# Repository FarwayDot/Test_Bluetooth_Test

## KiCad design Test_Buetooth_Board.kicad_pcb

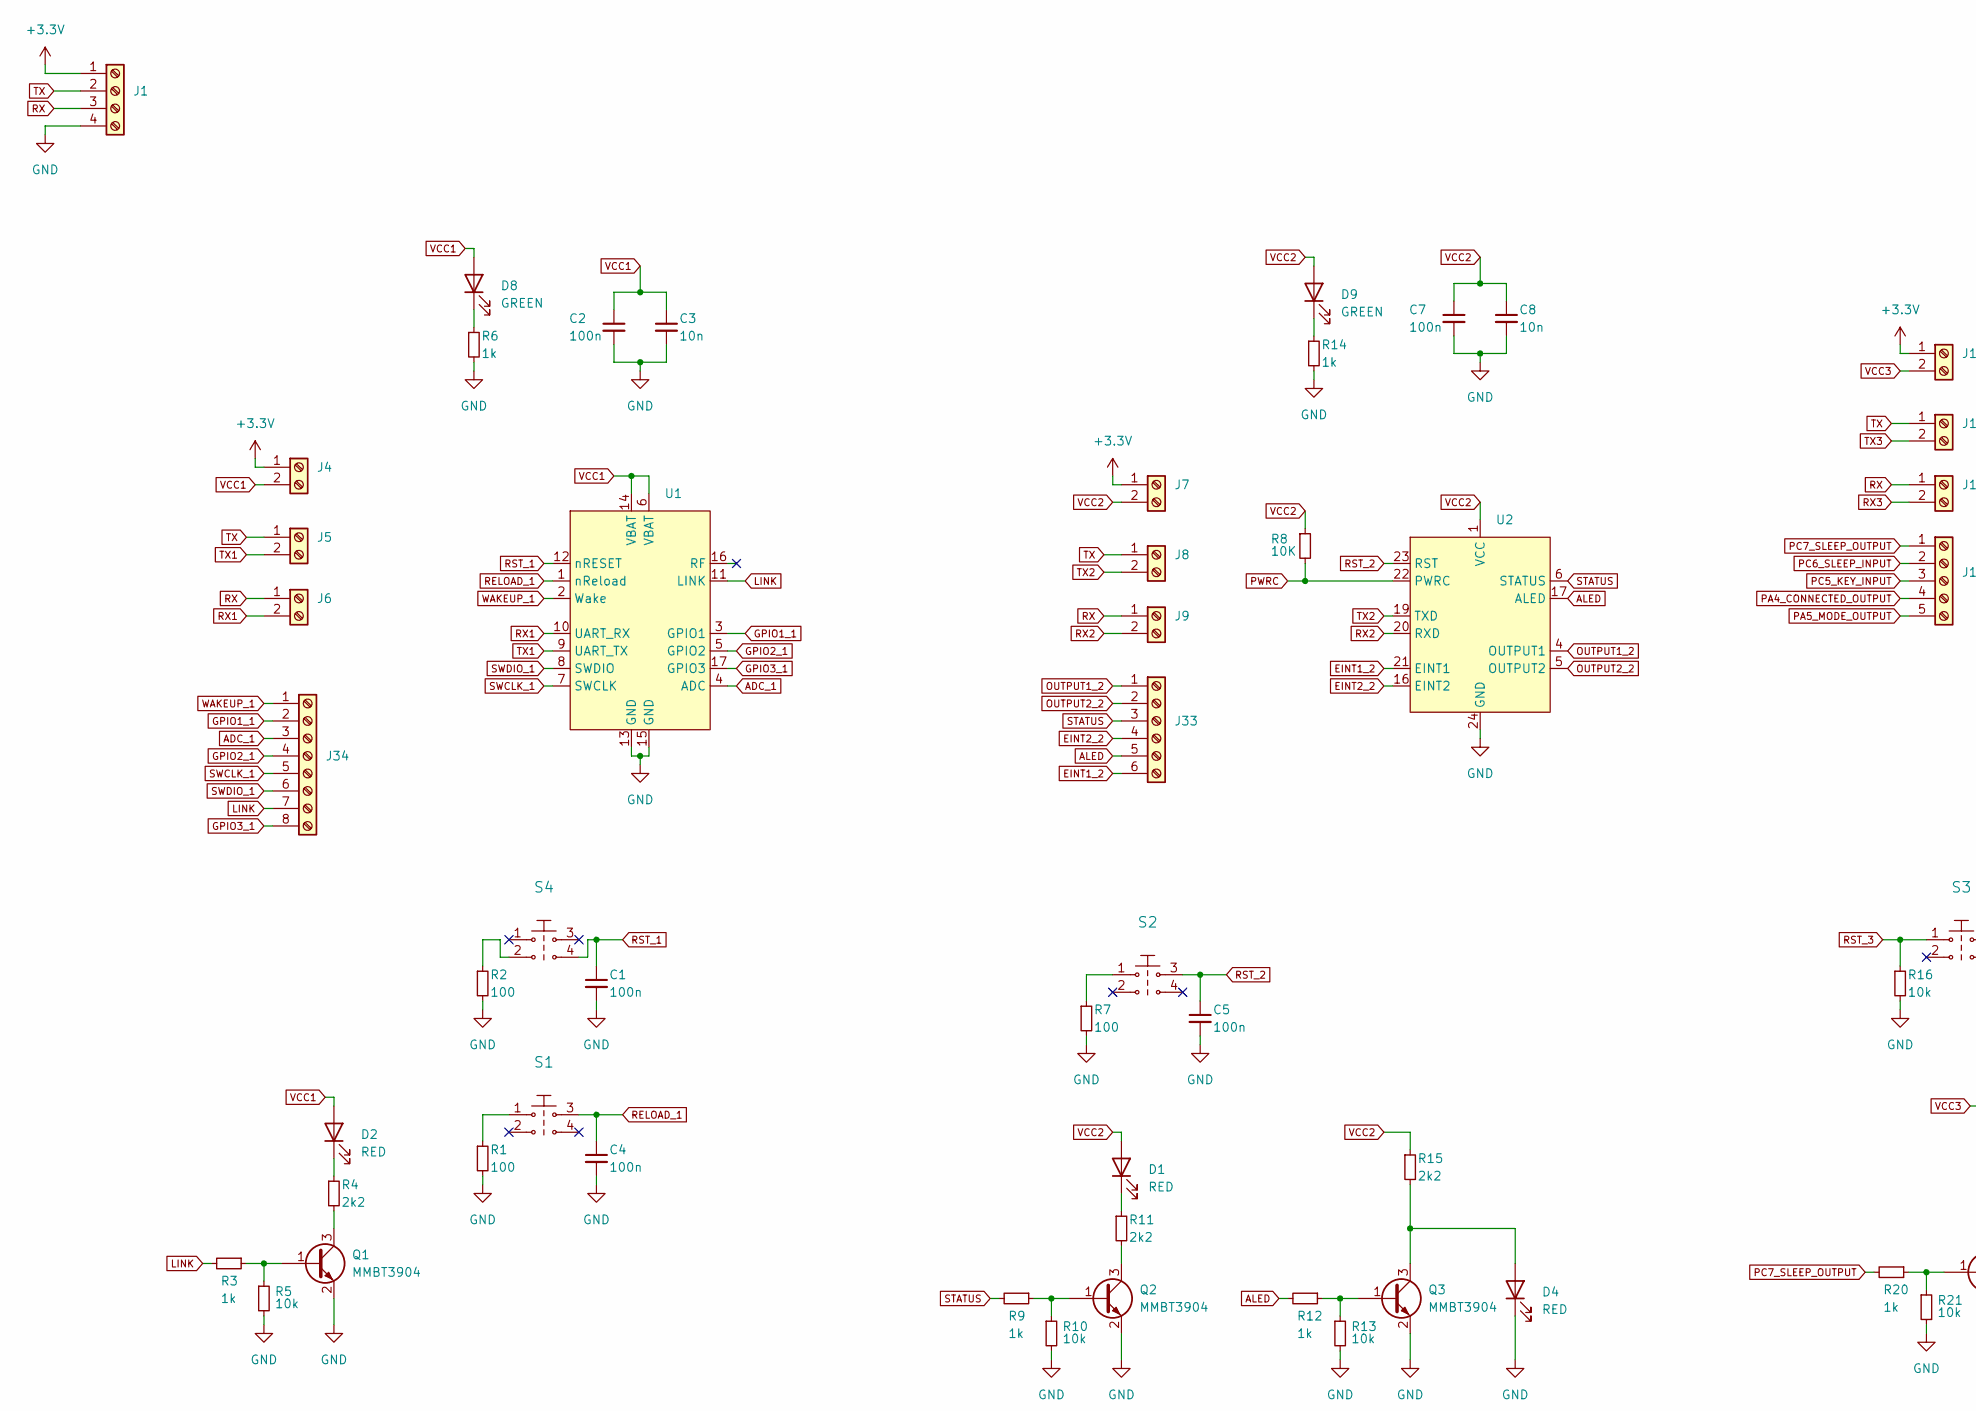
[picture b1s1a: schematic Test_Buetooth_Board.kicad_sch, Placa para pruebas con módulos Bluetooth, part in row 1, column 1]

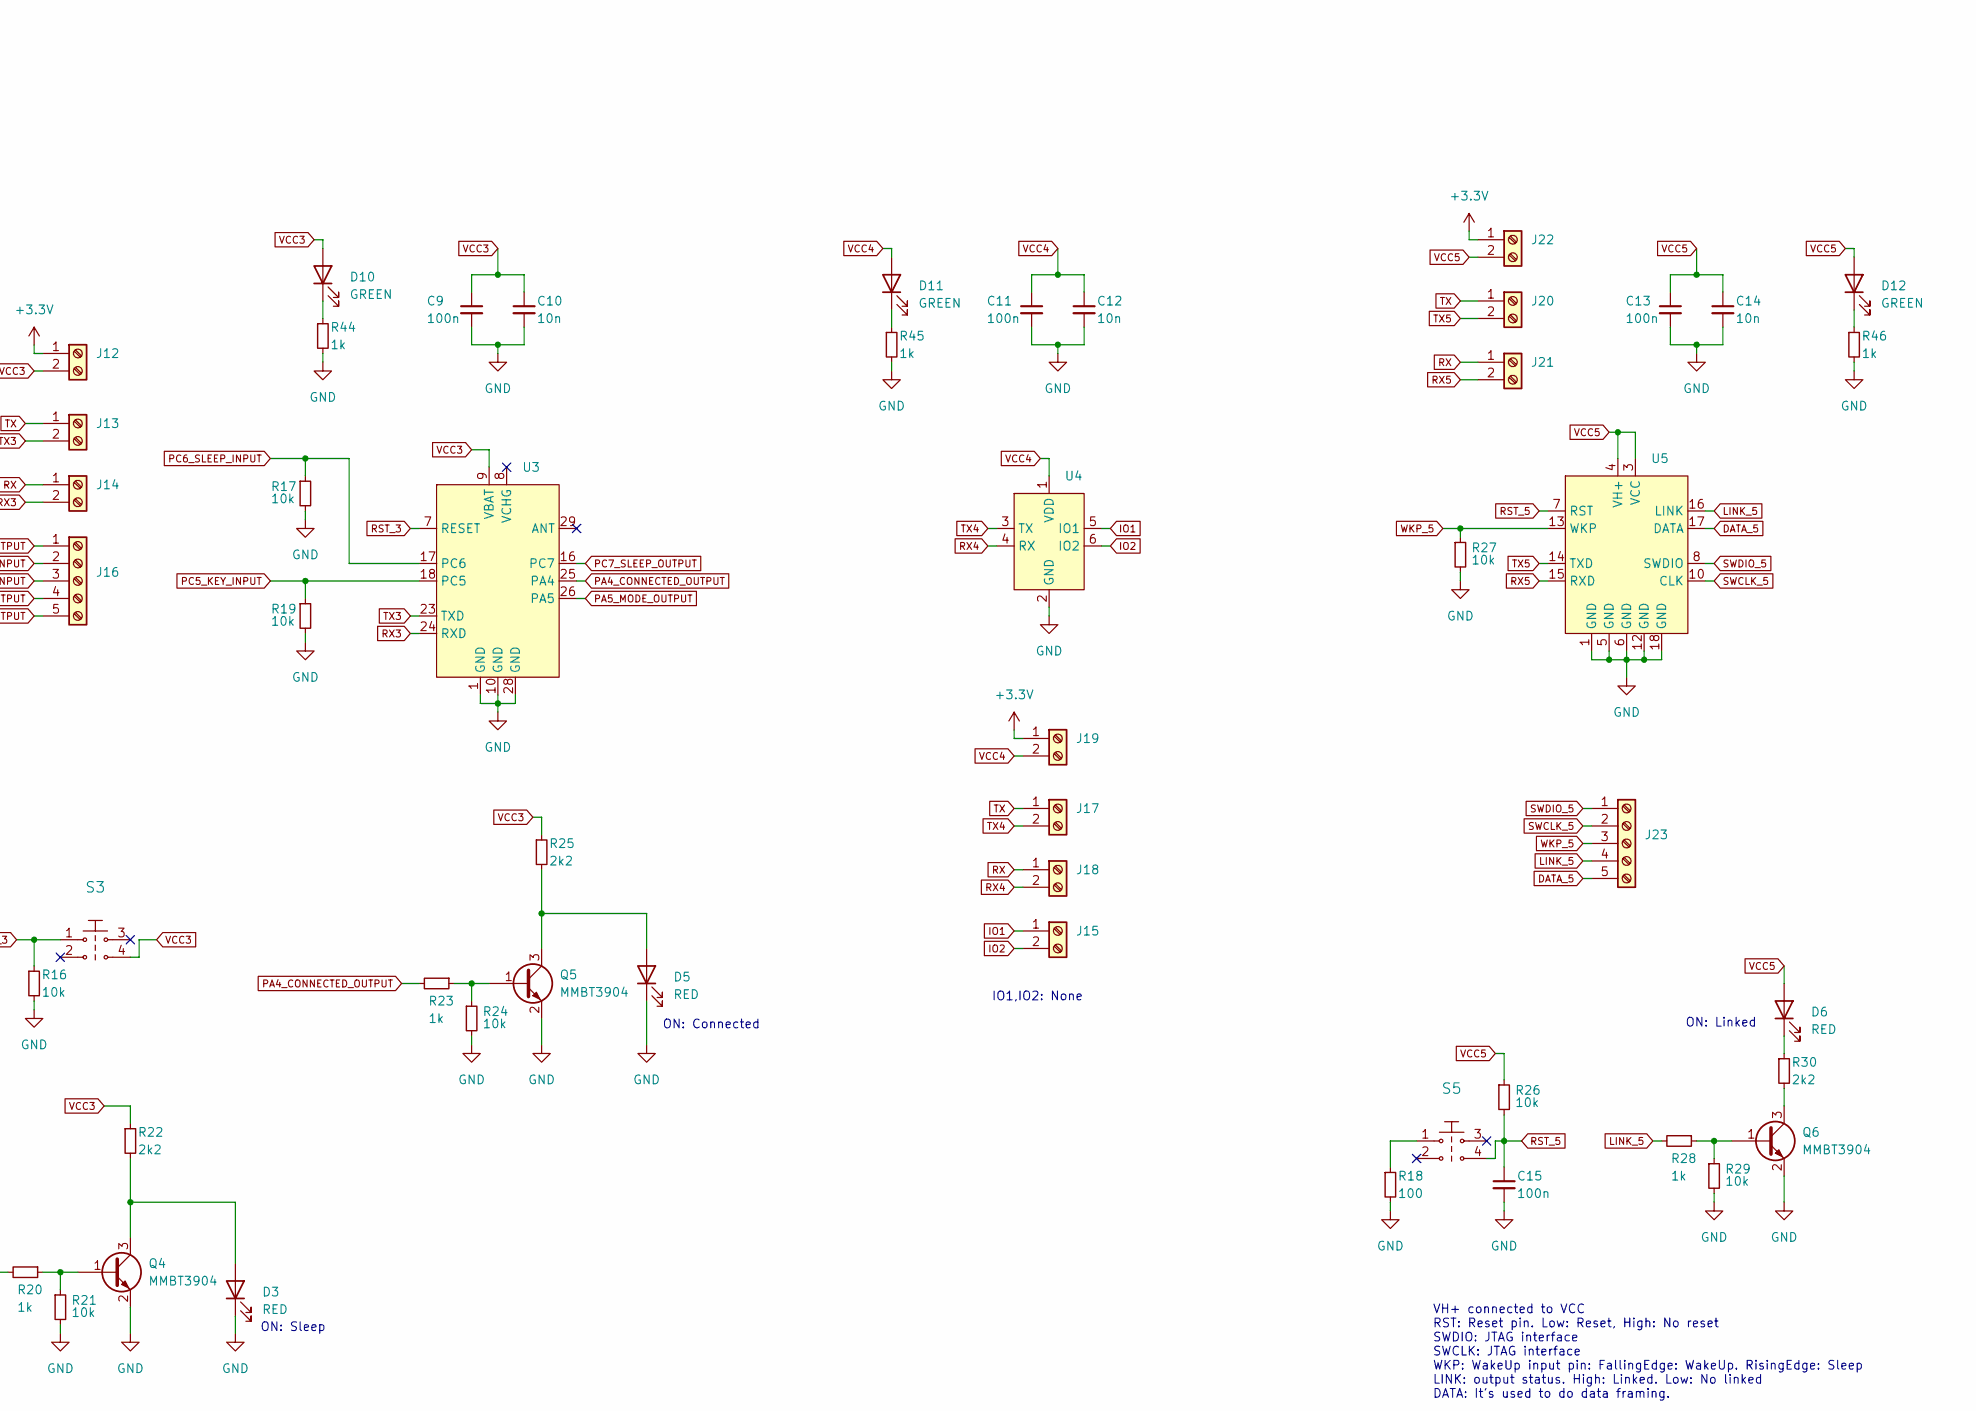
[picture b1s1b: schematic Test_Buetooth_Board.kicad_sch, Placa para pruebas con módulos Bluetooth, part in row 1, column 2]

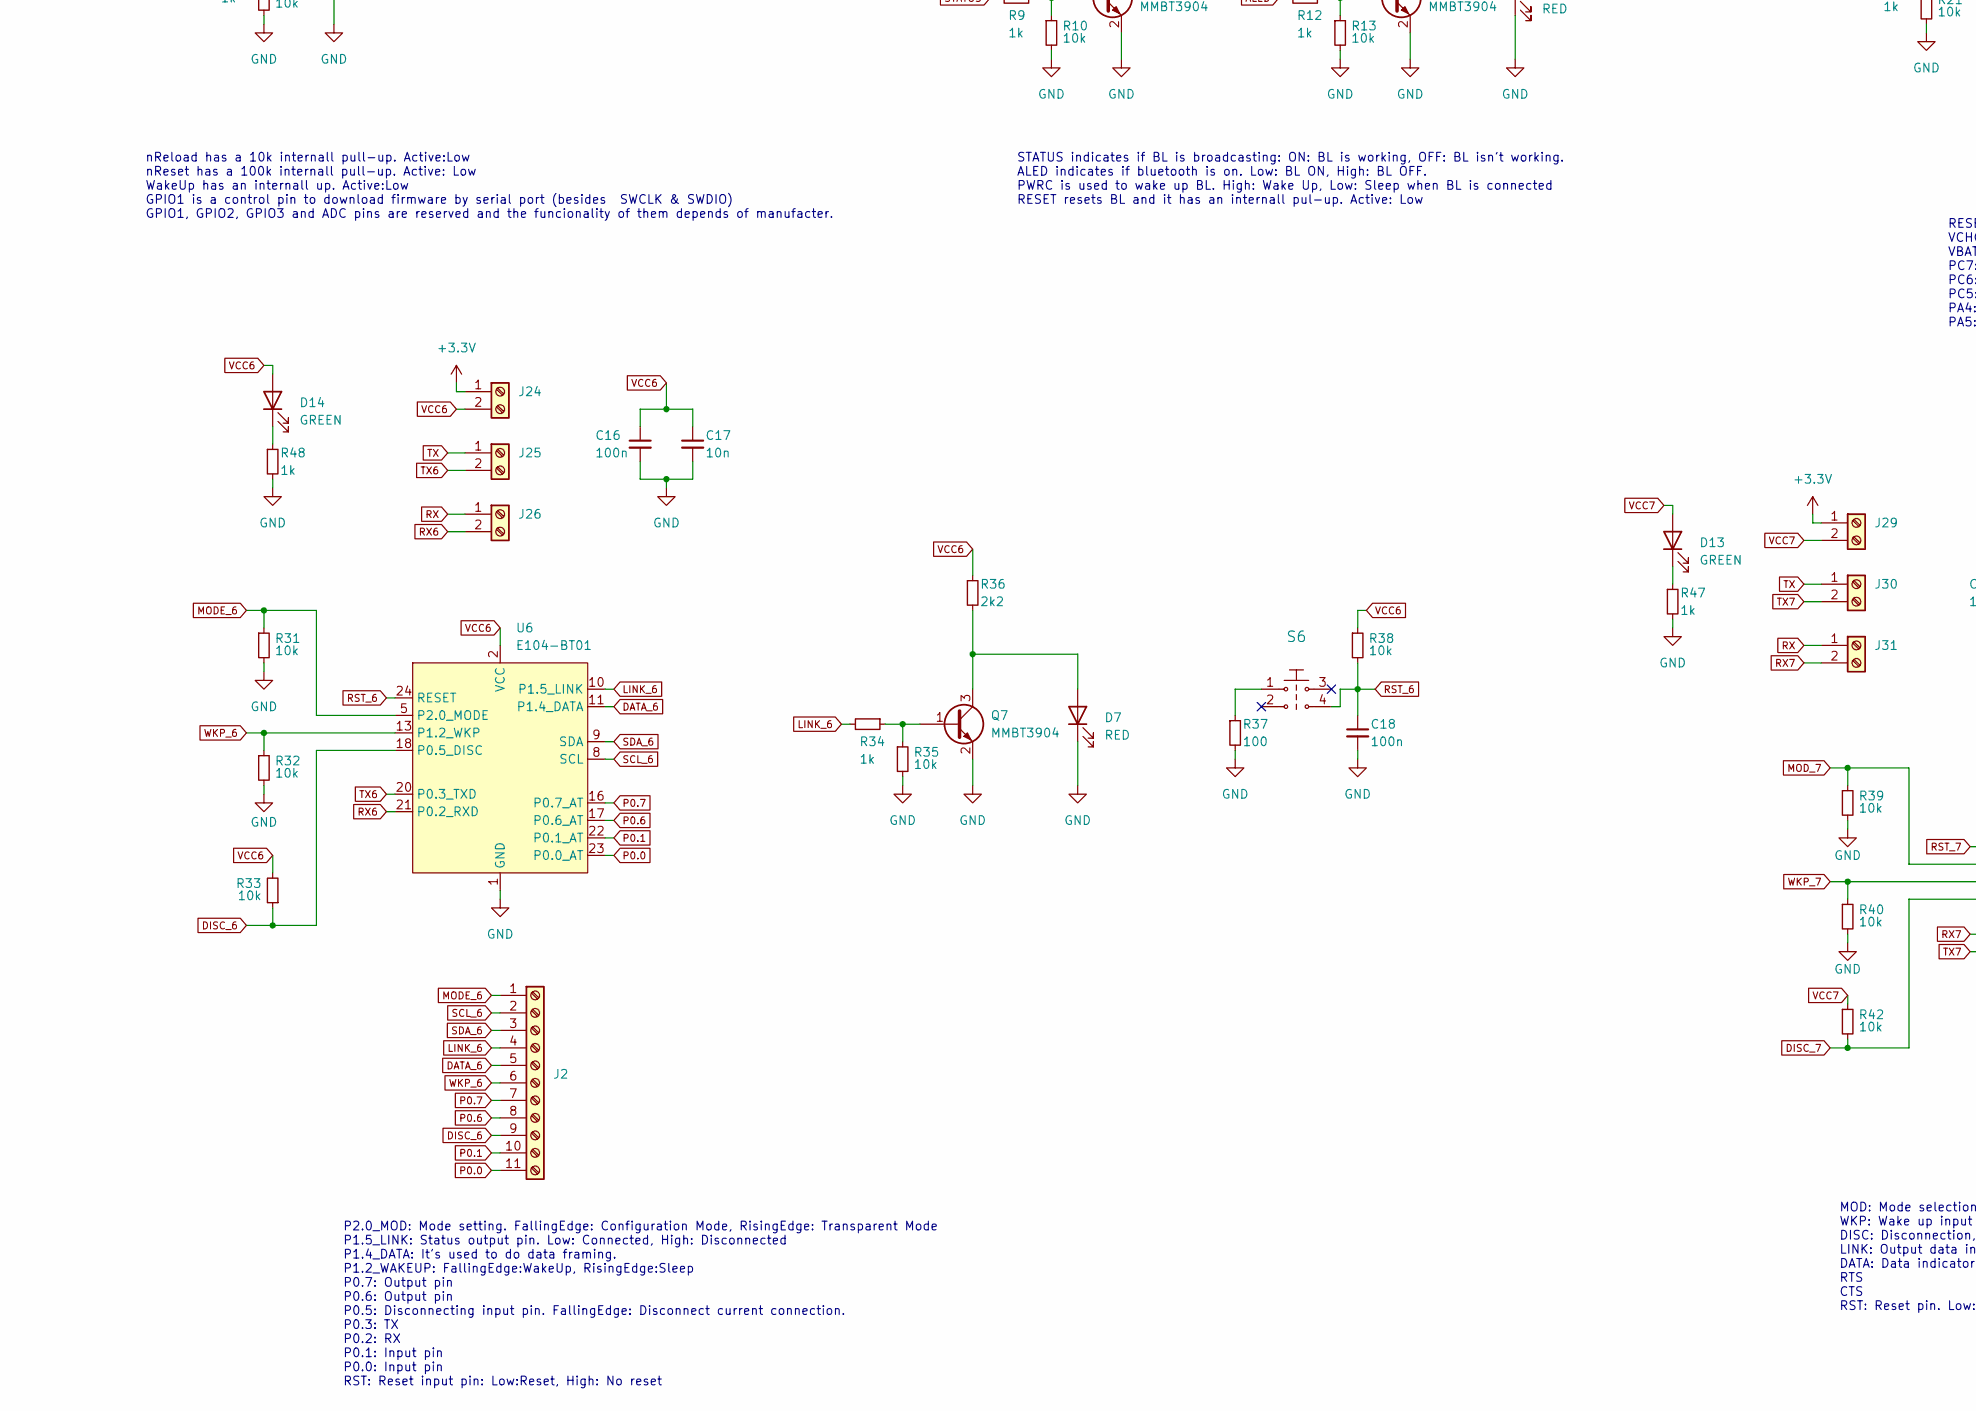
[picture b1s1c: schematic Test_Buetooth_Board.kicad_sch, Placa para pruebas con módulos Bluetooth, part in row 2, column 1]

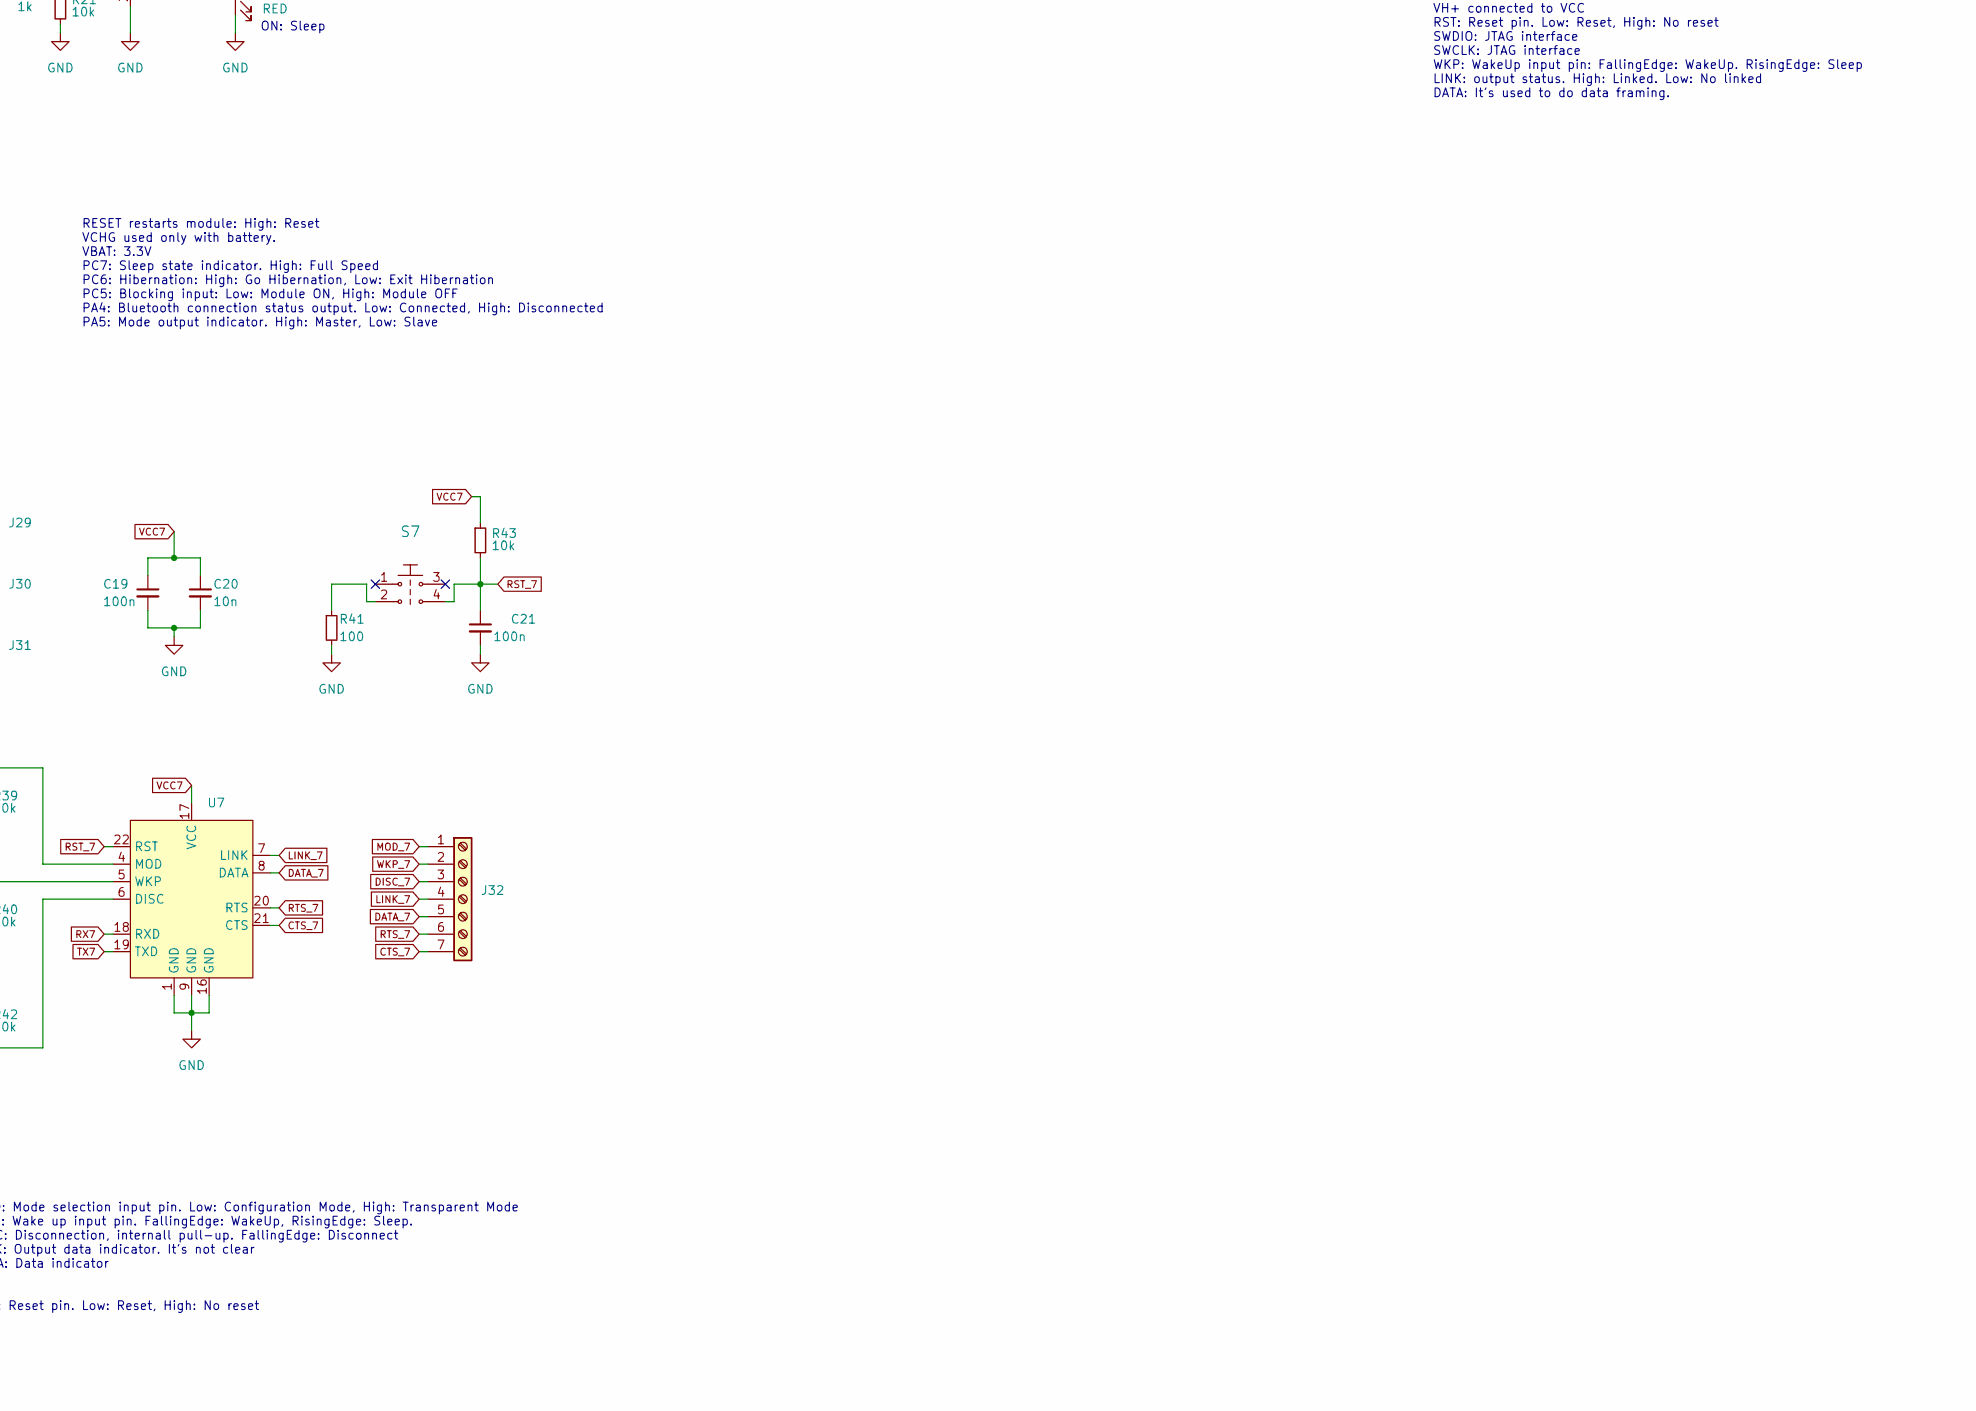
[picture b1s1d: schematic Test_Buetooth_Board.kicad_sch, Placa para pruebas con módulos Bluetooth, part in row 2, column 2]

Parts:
C1, C2, C4, C5, C7, C9, C11, C13, C15, C16, C18, C19, C21: 100n; C_0805_2012Metric
C3, C8, C10, C12, C14, C17, C20: 10n; C_0805_2012Metric
D1, D2, D3, D4, D5, D6, D7: RED; LED_0805
D8, D9, D10, D11, D12, D13, D14: GREEN; LED_0805
J1: Screw_Terminal_01x04; PinHeader_1x04_P2.54mm_Vertical
J2: Screw_Terminal_01x11; PinHeader_1x11_P2.54mm_Vertical
J4, J5, J6, J7, J8, J9, J12, J13, J14, J15, J17, J18, J19, J20, J21, J22, J24, J25, J26, J29, J30, J31: Screw_Terminal_01x02; PinHeader_1x02_P2.54mm_Vertical
J16, J23: Screw_Terminal_01x05; PinHeader_1x05_P2.54mm_Vertical
J32: Screw_Terminal_01x07; PinHeader_1x07_P2.54mm_Vertical
J33: Screw_Terminal_01x06; PinHeader_1x06_P2.54mm_Vertical
J34: Screw_Terminal_01x08; PinHeader_1x08_P2.54mm_Vertical
Q1, Q2, Q3, Q4, Q5, Q6, Q7: MMBT3904; SOT-23
R1, R2, R7, R18, R37, R41: 100; R_0805_2012Metric
R3, R6, R9, R12, R14, R20, R23, R28, R34, R44, R45, R46, R47, R48: 1k; R_0805_2012Metric
R4, R11, R15, R22, R25, R30, R36: 2k2; R_0805_2012Metric
R5, R10, R13, R16, R17, R19, R21, R24, R26, R27, R29, R31, R32, R33, R35, R38, R39, R40, R42, R43: 10k; R_0805_2012Metric
R8: 10K; R_0805_2012Metric
S1, S2, S3, S4, S5, S6, S7: SW_PUSH_6mm_H7.3mm; MPN B3U-1000P; Digi-Key_PN SW1020CT-ND
U1: WH-BLE103a
U2: YM23
U3: HLK-B40
U4: WL6601-TC
U5: E104-BT52
U6: E104-BT01
U7: E104-BT5010A

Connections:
+3.3V: J1.1, J4.1, J7.1, J12.1, J19.1, J22.1, J24.1, J29.1
ADC_1: J34.3, U1.4 (ADC)
ALED: J33.5, R12.2, U2.17 (ALED)
CTS_7: J32.7, U7.21 (CTS)
DATA_5: J23.5, U5.17 (DATA)
DATA_6: J2.5, U6.11 (P1.4_DATA)
DATA_7: J32.5, U7.8 (DATA)
DISC_6: J2.9, R33.1, U6.18 (P0.5_DISC)
DISC_7: J32.3, R42.2, U7.6 (DISC)
EINT1_2: J33.6, U2.21 (EINT1)
EINT2_2: J33.4, U2.16 (EINT2)
GND: C1.2, C2.2, C3.2, C4.2, C5.2, C7.2, C8.2, C9.2, C10.2, C11.2, C12.2, C13.2, C14.2, C15.2, C16.2, C17.2, C18.2, C19.2, C20.2, C21.2, D3.1 (K), D4.1 (K), D5.1 (K), D7.1 (K), J1.4, Q1.2 (E), Q2.2 (E), Q3.2 (E), Q4.2 (E), Q5.2 (E), Q6.2 (E), Q7.2 (E), R1.2, R2.2, R5.2, R6.2, R7.2, R10.2, R13.2, R14.2, R16.2, R17.2, R18.2, R19.2, R21.2, R24.2, R27.2, R29.2, R31.2, R32.2, R35.2, R37.2, R39.2, R40.2, R41.2, R44.2, R45.2, R46.2, R47.2, R48.2, U1.13 (GND), U1.15 (GND), U2.24 (GND), U3.1 (GND), U3.10 (GND), U3.28 (GND), U4.2 (GND), U5.1 (GND), U5.5 (GND), U5.6 (GND), U5.12 (GND), U5.18 (GND), U6.1 (GND), U7.1 (GND), U7.9 (GND), U7.16 (GND)
GPIO1_1: J34.2, U1.3 (GPIO1)
GPIO2_1: J34.4, U1.5 (GPIO2)
GPIO3_1: J34.8, U1.17 (GPIO3)
IO1: J15.1, U4.5 (IO1)
IO2: J15.2, U4.6 (IO2)
LINK: J34.7, R3.2, U1.11 (LINK)
LINK_5: J23.4, R28.2, U5.16 (LINK)
LINK_6: J2.4, R34.2, U6.10 (P1.5_LINK)
LINK_7: J32.4, U7.7 (LINK)
MODE_6: J2.1, R31.1, U6.5 (P2.0_MODE)
MOD_7: J32.1, R39.1, U7.4 (MOD)
unnamed: D1.1 (K), R11.1
unnamed: D2.1 (K), R4.1
unnamed: D3.2 (A), Q4.3 (C), R22.2
unnamed: D4.2 (A), Q3.3 (C), R15.2
unnamed: D5.2 (A), Q5.3 (C), R25.2
unnamed: D6.1 (K), R30.1
unnamed: D7.2 (A), Q7.3 (C), R36.2
unnamed: D8.1 (K), R6.1
unnamed: D9.1 (K), R14.1
unnamed: D10.1 (K), R44.1
unnamed: D11.1 (K), R45.1
unnamed: D12.1 (K), R46.1
unnamed: D13.1 (K), R47.1
unnamed: D14.1 (K), R48.1
unnamed: Q1.1 (B), R3.1, R5.1
unnamed: Q1.3 (C), R4.2
unnamed: Q2.1 (B), R9.1, R10.1
unnamed: Q2.3 (C), R11.2
unnamed: Q3.1 (B), R12.1, R13.1
unnamed: Q4.1 (B), R20.1, R21.1
unnamed: Q5.1 (B), R23.1, R24.1
unnamed: Q6.1 (B), R28.1, R29.1
unnamed: Q6.3 (C), R30.2
unnamed: Q7.1 (B), R34.1, R35.1
unnamed: R1.1, S1.1
unnamed: R2.1, S4.2
unnamed: R7.1, S2.1
unnamed: R18.1, S5.1
unnamed: R37.1, S6.1
unnamed: R41.1, S7.2
OUTPUT1_2: J33.1, U2.4 (OUTPUT1)
OUTPUT2_2: J33.2, U2.5 (OUTPUT2)
P0.0: J2.11, U6.23 (P0.0_AT)
P0.1: J2.10, U6.22 (P0.1_AT)
P0.6: J2.8, U6.17 (P0.6_AT)
P0.7: J2.7, U6.16 (P0.7_AT)
PA4_CONNECTED_OUTPUT: J16.4, R23.2, U3.25 (PA4)
PA5_MODE_OUTPUT: J16.5, U3.26 (PA5)
PC5_KEY_INPUT: J16.3, R19.1, U3.18 (PC5)
PC6_SLEEP_INPUT: J16.2, R17.1, U3.17 (PC6)
PC7_SLEEP_OUTPUT: J16.1, R20.2, U3.16 (PC7)
PWRC: R8.2, U2.22 (PWRC)
RELOAD_1: C4.1, S1.3, U1.1 (nReload)
RST_1: C1.1, S4.4, U1.12 (nRESET)
RST_2: C5.1, S2.3, U2.23 (RST)
RST_3: R16.1, S3.1, U3.7 (RESET)
RST_5: C15.1, R26.2, S5.4, U5.7 (RST)
RST_6: C18.1, R38.2, S6.4, U6.24 (RESET)
RST_7: C21.1, R43.2, S7.4, U7.22 (RST)
RTS_7: J32.6, U7.20 (RTS)
RX: J1.3, J6.1, J9.1, J14.1, J18.1, J21.1, J26.1, J31.1
RX1: J6.2, U1.10 (UART_RX)
RX2: J9.2, U2.20 (RXD)
RX3: J14.2, U3.24 (RXD)
RX4: J18.2, U4.4 (RX)
RX5: J21.2, U5.15 (RXD)
RX6: J26.2, U6.21 (P0.2_RXD)
RX7: J31.2, U7.18 (RXD)
SCL_6: J2.2, U6.8 (SCL)
SDA_6: J2.3, U6.9 (SDA)
STATUS: J33.3, R9.2, U2.6 (STATUS)
SWCLK_1: J34.5, U1.7 (SWCLK)
SWCLK_5: J23.2, U5.10 (CLK)
SWDIO_1: J34.6, U1.8 (SWDIO)
SWDIO_5: J23.1, U5.8 (SWDIO)
TX: J1.2, J5.1, J8.1, J13.1, J17.1, J20.1, J25.1, J30.1
TX1: J5.2, U1.9 (UART_TX)
TX2: J8.2, U2.19 (TXD)
TX3: J13.2, U3.23 (TXD)
TX4: J17.2, U4.3 (TX)
TX5: J20.2, U5.14 (TXD)
TX6: J25.2, U6.20 (P0.3_TXD)
TX7: J30.2, U7.19 (TXD)
VCC1: C2.1, C3.1, D2.2 (A), D8.2 (A), J4.2, U1.6 (VBAT), U1.14 (VBAT)
VCC2: C7.1, C8.1, D1.2 (A), D9.2 (A), J7.2, R8.1, R15.1, U2.1 (VCC)
VCC3: C9.1, C10.1, D10.2 (A), J12.2, R22.1, R25.1, S3.4, U3.9 (VBAT)
VCC4: C11.1, C12.1, D11.2 (A), J19.2, U4.1 (VDD)
VCC5: C13.1, C14.1, D6.2 (A), D12.2 (A), J22.2, R26.1, U5.3 (VCC), U5.4 (VH+)
VCC6: C16.1, C17.1, D14.2 (A), J24.2, R33.2, R36.1, R38.1, U6.2 (VCC)
VCC7: C19.1, C20.1, D13.2 (A), J29.2, R42.1, R43.1, U7.17 (VCC)
WAKEUP_1: J34.1, U1.2 (Wake)
WKP_5: J23.3, R27.1, U5.13 (WKP)
WKP_6: J2.6, R32.1, U6.13 (P1.2_WKP)
WKP_7: J32.2, R40.1, U7.5 (WKP)

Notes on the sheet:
ON: Linked
MOD: Mode selection input pin. Low: Configuration Mode, High: Transparent Mode WKP: Wake up input pin. FallingEdge: WakeUp, RisingEdge: Sleep. DISC: Disconnection, internall pull-up. FallingEdge: Disconnect LINK: Output data indicator. It's not clear DATA: Data indicator RTS CTS RST: Reset pin. Low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
STATUS indicates if BL is broadcasting: ON: BL is working, OFF: BL isn't working. ALED indicates if bluetooth is on. Low: BL ON, High: BL OFF. PWRC is used to wake up BL. High: Wake Up, Low: Sleep when BL is connected RESET resets BL and it has an internall pul-up. Active: Low
ON: Sleep
RESET restarts module: High: Reset VCHG used only with battery. VBAT: 3.3V PC7: Sleep state indicator. High: Full Speed PC6: Hibernation: High: Go Hibernation, Low: Exit Hibernation PC5: Blocking input: Low: Module ON, High: Module OFF PA4: Bluetooth connection status output. Low: Connected, High: 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
nReload has a 10k internall pull-up. Active:Low nReset has a 100k internall pull-up. Active: Low WakeUp has an internall up. Active:Low GPIO1 is a control pin to download firmware by serial port (besides SWCLK & SWDIO) GPIO1, GPIO2, GPIO3 and ADC pins are reserved and the funcionality of them depen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
VH+ connected to VCC RST: Reset pin. Low: Reset, High: No reset SWDIO: JTAG interface SWCLK: JTAG interface WKP: WakeUp input pin: FallingEdge: WakeUp. RisingEdge: Sleep LINK: output status. High: Linked. Low: No linked DATA: It's used to do data framing.
P2.0_MOD: Mode setting. FallingEdge: Configuration Mode, RisingEdge: Transparent Mode P1.5_LINK: Status output pin. Low: Connected, High: Disconnected P1.4_DATA: It's used to do data framing. P1.2_WAKEUP: FallingEdge:WakeUp, RisingEdge:Sleep P0.7: Output pin P0.6: Output pin P0.5: Disconnecting inp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
ON: Connected
IO1,IO2: None

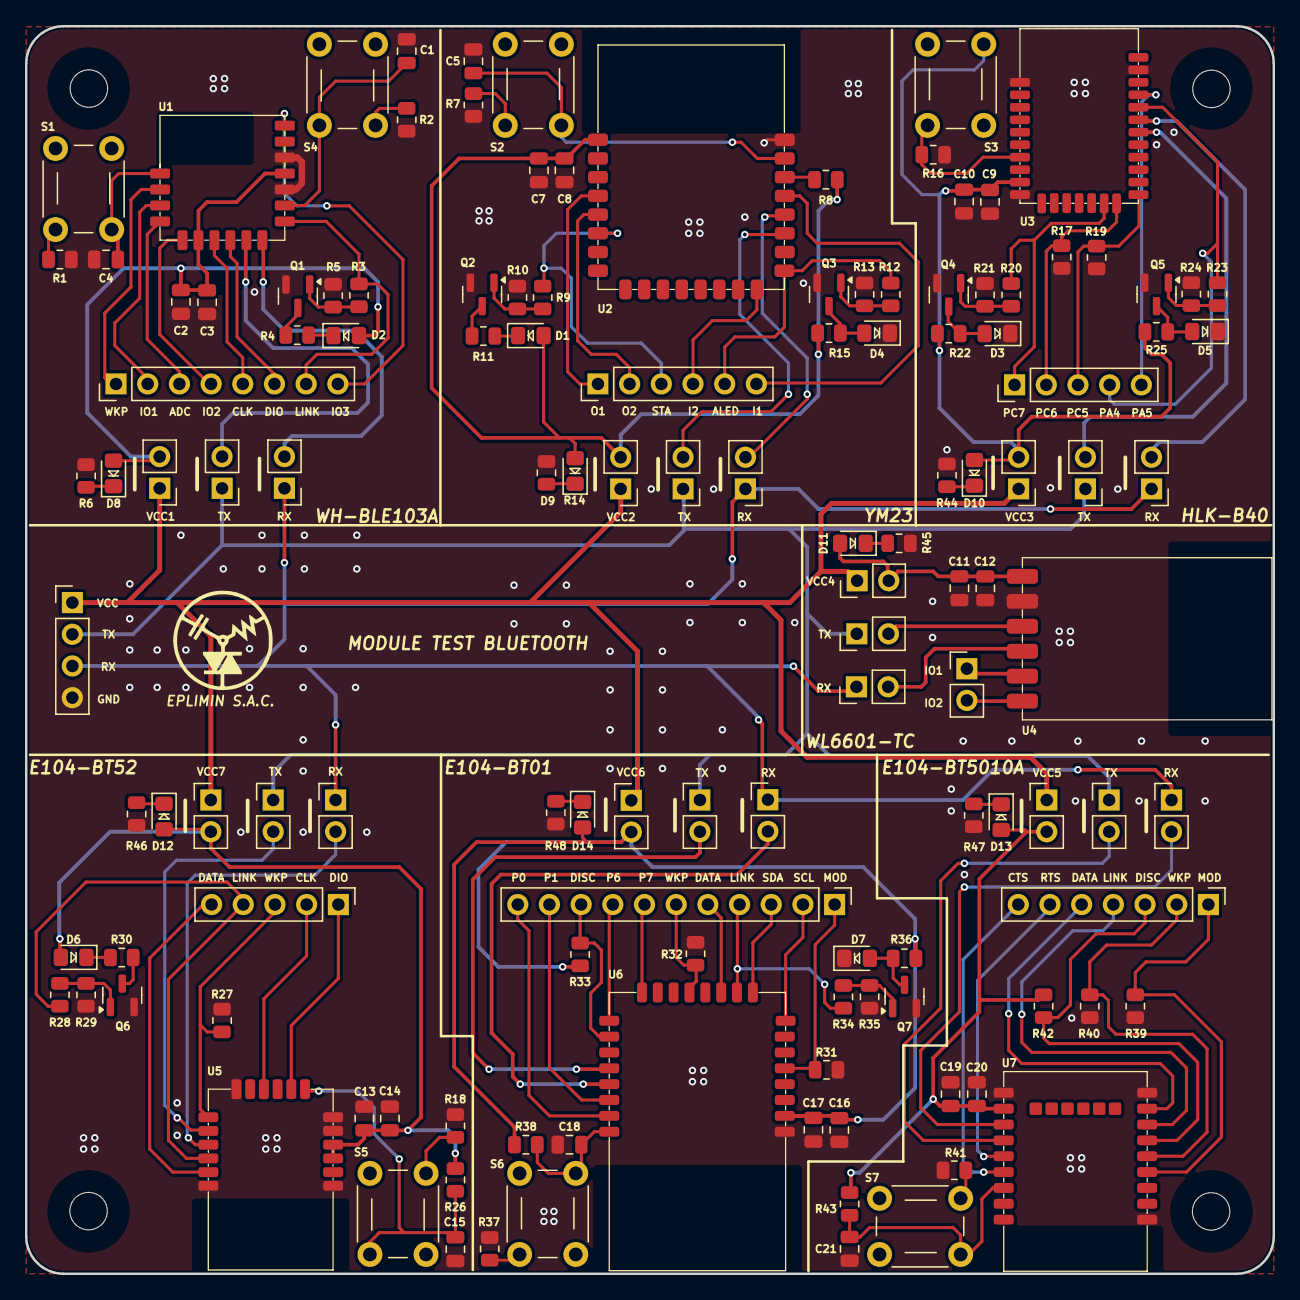
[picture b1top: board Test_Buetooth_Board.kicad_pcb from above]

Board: 2 copper layers, 100.0 x 100.0 mm, 133 parts (0 on the bottom side), 107 nets.

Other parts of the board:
G1: LOGO

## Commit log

2024-05-13 SCH: Se termina la primera versión del sch. PCB: Se ordenan unos componentes
2024-05-13 Acance del PCB, se acomoda la mayoría de componentes
2024-05-14 Se añade descripción a la cajetilla y se unen dos headers en uno
2024-05-14 Se acaba de colocar un header por cada placa para probar en otra próxima rama la utilidad, en main seguiremos con el planteamiento inicial de utiizar jumpers
2024-05-14 SCH: Se modificaron VCC que no estaban en el orden correcto, re remplaza la librería del pulsador, se areglan otros errores, tener en cuenta para la otra rama o eliminarla. PCB: Ruteado, falta termin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
2024-06-10 SCH: Se corrige una etiqueta. PCB: Se añaden y ordenan las referencias. JLC: No hay cambios
2024-06-11 SCH: Se agregan leds para el VCC de cada módulo, se cambia la librería del pulsador. se mueven posiciones. PCB: Se agrega serigrafía, se agregan vías gnd, se modifica GND, se resuelven los errores. J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
